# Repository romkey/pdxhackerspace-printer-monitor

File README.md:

# PDX Hackerspace 3D Printer Monitor

This is a simple device for monitoring 3D printers.

It hosts a [SeeedStudio Xiao ESP32S3 Sense](https://www.seeedstudio.com/XIAO-ESP32S3-Sense-p-5639.html) CPU camera module so that its users can see the status of their prints.

It also can use a BME280 or BME680 for environmental (air temperature and humidity) monitoring, as well as a PMS5003 for air quality/particulate matter.

It includes an optional connection to an I2C display or a larger SPI-based RGB display, and can drive an addressable RGB LED strip for lighting.

## Modifying the Xiao S3 Sense

The Xiao S3 Sense has optional D11 and D12 pins. We can use these pins
to provide PWM signals to control an optional air filter fan, and to
run optional RGB LEDs on the fan. These signals are run through the
level shifter to bring them to 5V values.

Because we've run out of pins we need to use D11 and D12. By default
they're connected to the Xiao camera board's I2S microphone. The board
needs to be modified as documented
[here](https://wiki.seeedstudio.com/xiao_esp32s3_pin_multiplexing/#step-1-cut-off-the-connection-between-j1-and-j2).
Note that this web page incorrectly states the GPIO numbers for D11
and D12. D11 is actually GPIO42 and D12 is actually GPIO41.

## PCB

The PCB is designed using KiCAD. Hardware revisions are stored in the hardware directory.

You can [order this PCB from OSHPark](https://oshpark.com/shared_projects/bLoBvODi) but please don't order it. This project is under active albeit slow development. There will be a better version available soon.

## Software

The board is intended to integrate with Home Assistant. ESPHome is the easiest way to build code for it. The repo contains an example ESPHome definition file at esphome.yml, which needs its display functionality fleshed out.

## OV5640

https://github.com/0015/ESP32-OV5640-AF

## PrusaLink

Status observed:
- finished
- idle
- busy
- attention
- printing

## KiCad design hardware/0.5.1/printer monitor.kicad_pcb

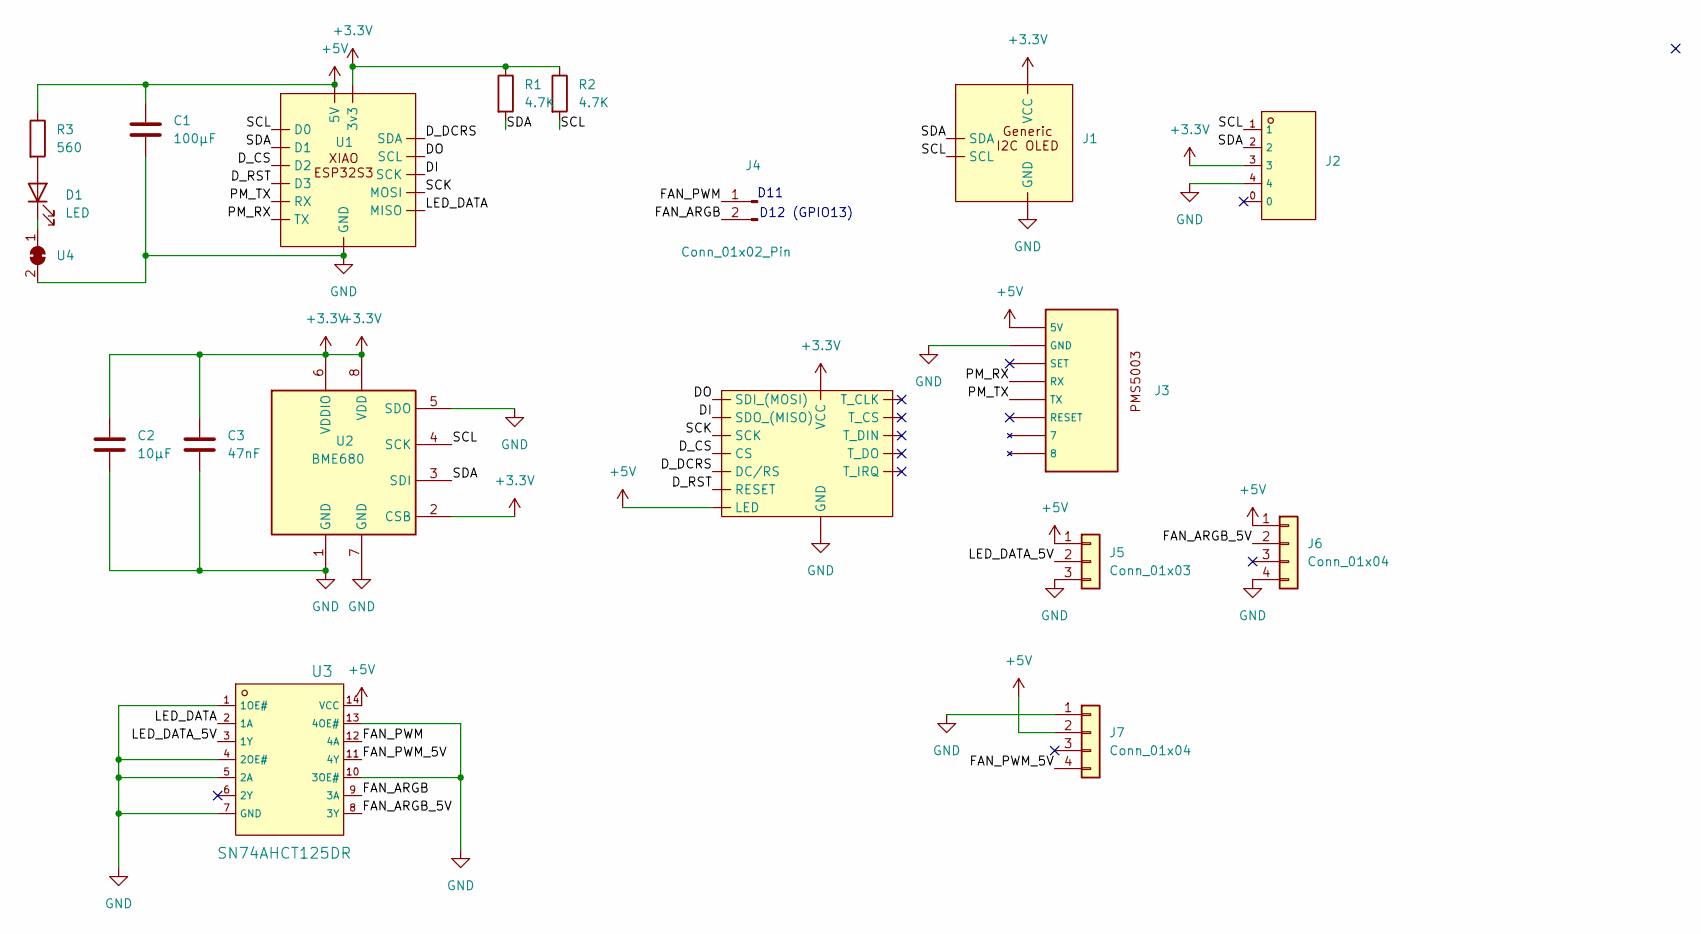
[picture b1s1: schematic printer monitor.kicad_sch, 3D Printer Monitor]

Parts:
C1: 100µF; CP_Elec_6.3x5.7; MPN C5155334
C2: 10µF; C_0805_2012Metric_Pad1.18x1.45mm_HandSolder; MPN C342724
C3: 47nF; C_0603_1608Metric_Pad1.08x0.95mm_HandSolder; MPN C123512
D1: LED; LED_1206_3216Metric_Pad1.42x1.75mm_HandSolder; MPN C375482
J1: Generic I2C OLED
J2: CONN-SMD_BM04B-SRSS-TB; MPN C160390; LCSC C160390
J3: PMS5003 Connector
J4: Conn_01x02_Pin; PinSocket_1x02_P2.54mm_Vertical
J5: Conn_01x03; PinSocket_1x03_P2.54mm_Vertical
J6, J7: Conn_01x04; PinSocket_1x04_P2.54mm_Vertical
R1, R2: 4.7K; R_0805_2012Metric_Pad1.20x1.40mm_HandSolder; MPN C105427
R3: 560; R_1206_3216Metric_Pad1.30x1.75mm_HandSolder; MPN С319525
U1: Xiao ESP32S3 Sense (Camera)
U2: BME680; Bosch_LGA-8_3x3mm_P0.8mm_ClockwisePinNumbering; MPN C125972
U3: SN74AHCT125DR; SOIC-14_L8.7-W3.9-P1.27-LS6.0-BL; MPN C155176; LCSC C155176
U4: SolderJumper-2_P1.3mm_Bridged_RoundedPad1.0x1.5mm
U5: SPI_TFT_TOUCH

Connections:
+3.3V: C2.1, C3.1, J1.4 (VCC), J2.3, R1.1, R2.1, U1.12 (3v3), U2.2 (CSB), U2.6 (VDDIO), U2.8 (VDD), U5.1 (VCC)
+5V: C1.1, J3.1 (5V), J5.1, J6.1, J7.2, R3.1, U1.14 (5V), U3.14 (VCC), U5.8 (LED)
/DI: U1.9 (SCK), U5.9 (SDO_(MISO))
/DO: U1.6 (SCL), U5.6 (SDI_(MOSI))
/D_CS: U1.3 (D2), U5.3 (CS)
/D_DCRS: U1.5 (SDA), U5.5 (DC/RS)
/D_RST: U1.4 (D3), U5.4 (RESET)
/FAN_ARGB: J4.2, U3.9 (3A)
/FAN_ARGB_5V: J6.2, U3.8 (3Y)
/FAN_PWM: J4.1, U3.12 (4A)
/FAN_PWM_5V: J7.4, U3.11 (4Y)
/LED_DATA: U1.10 (MISO), U3.2 (1A)
/LED_DATA_5V: J5.2, U3.3 (1Y)
/PM_RX: J3.4 (RX), U1.7 (TX)
/PM_TX: J3.5 (TX), U1.8 (RX)
/SCK: U1.11 (MOSI), U5.7 (SCK)
/SCL: J1.2 (SCL), J2.1, R2.2, U1.1 (D0), U2.4 (SCK)
/SDA: J1.1 (SDA), J2.2, R1.2, U1.2 (D1), U2.3 (SDI)
GND: C1.2, C2.2, C3.2, J1.3 (GND), J2.4, J3.2 (GND), J5.3, J6.4, J7.1, U1.13 (GND), U2.1 (GND), U2.5 (SDO), U2.7 (GND), U3.1 (1OE#), U3.4 (2OE#), U3.5 (2A), U3.7 (GND), U3.10 (3OE#), U3.13 (4OE#), U4.2 (B), U5.2 (GND)
unnamed: D1.2 (A), R3.2
unnamed: D1.1 (K), U4.1 (A)

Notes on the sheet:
D11
D12 (GPIO13)

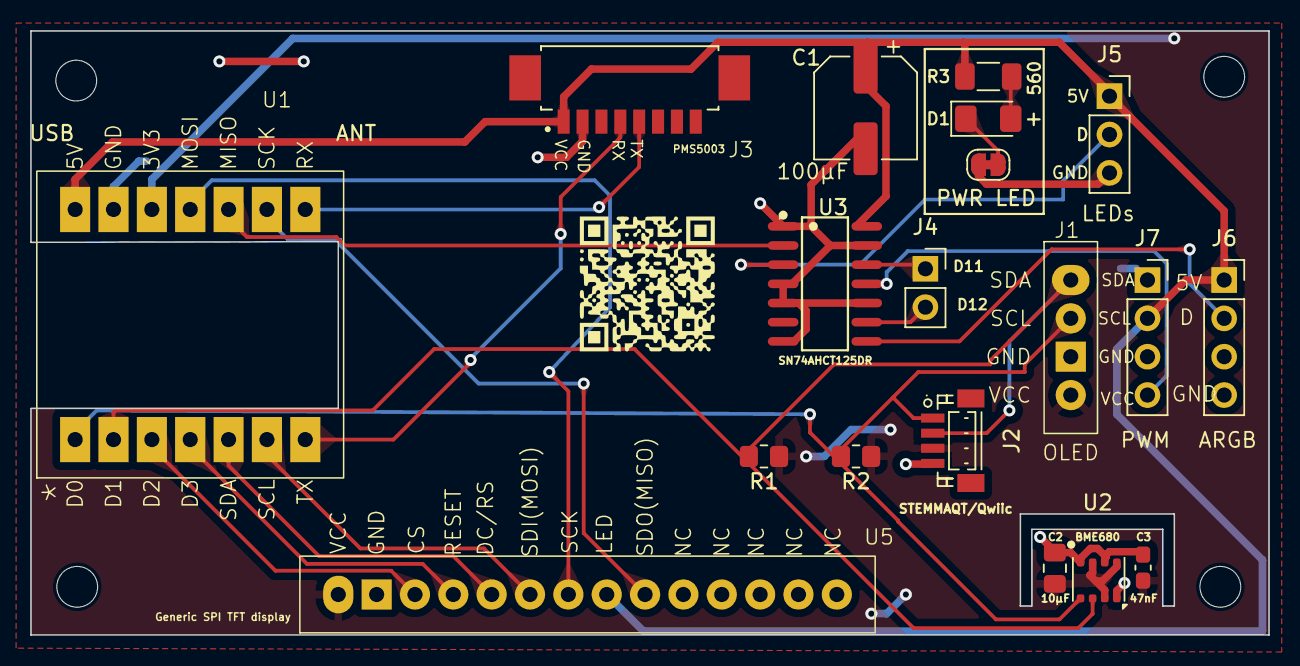
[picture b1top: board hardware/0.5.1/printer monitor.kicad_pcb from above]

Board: 2 copper layers, 82.0 x 40.0 mm, 23 parts (0 on the bottom side), 21 nets.

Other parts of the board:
H1, H2, H3, H4: MountingHole; MountingHole_2.7mm_M2.5

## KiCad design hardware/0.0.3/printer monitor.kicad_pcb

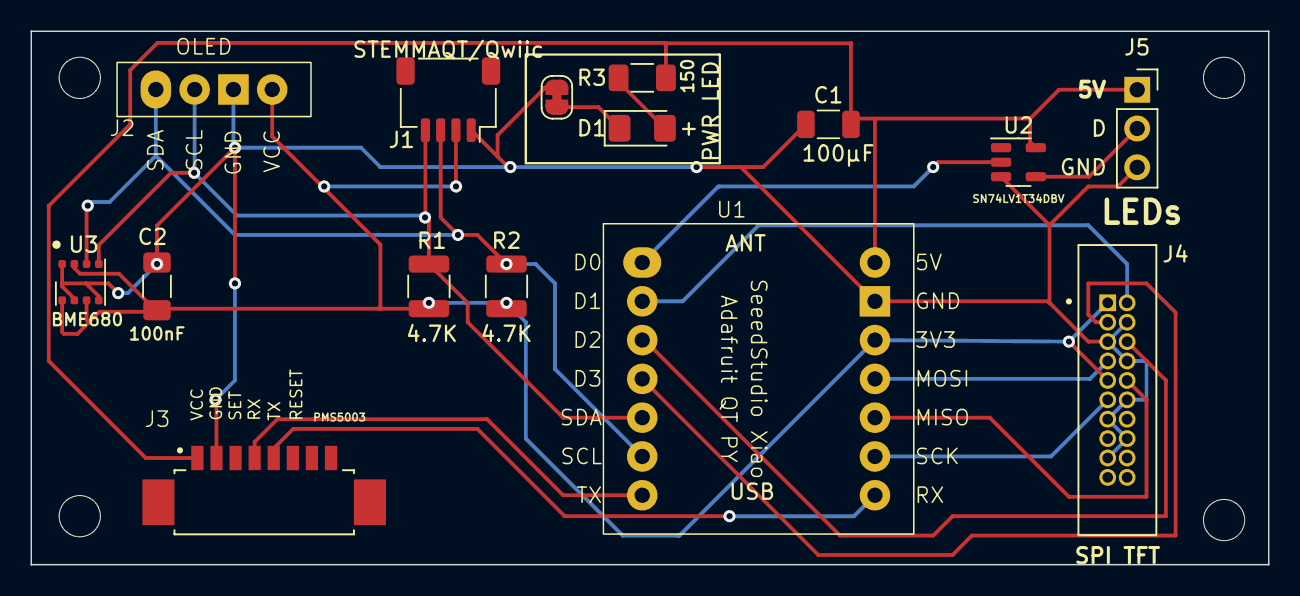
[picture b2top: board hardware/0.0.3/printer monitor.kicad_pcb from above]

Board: 2 copper layers, 81.0 x 34.9 mm, 19 parts (0 on the bottom side), 17 nets.

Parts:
C1: 100µF; C_1206_3216Metric
C2: 100nF; C_1206_3216Metric_Pad1.33x1.80mm_HandSolder
D1: LED; LED_1206_3216Metric_Pad1.42x1.75mm_HandSolder
H1, H2, H3, H4: MountingHole; MountingHole_2.7mm_M2.5
J1: JST_SH_SM04B-SRSS-TB_1x04-1MP_P1.00mm_Horizontal
J2: Generic I2C OLED
J3: PMS5003 Connector
J4: Conn_01x20; AMPHENOL_20021511-00020T4LF
J5: Conn_01x03; PinSocket_1x03_P2.54mm_Vertical
R1, R2: 4.7K; R_1210_3225Metric
R3: 150; R_1206_3216Metric_Pad1.30x1.75mm_HandSolder
U1: Xiao ESP32S3
U2: SN74LV1T34DBV; SOT-23-5
U3: BME680; Bosch_LGA-8_3x3mm_P0.8mm_ClockwisePinNumbering
U4: SolderJumper-2_P1.3mm_Bridged_RoundedPad1.0x1.5mm

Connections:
+3.3V: C2.1, J1.2 (VCC), J2.4 (VCC), J4.1, J4.9, R1.1, R2.1, U1.12 (3v3), U3.2 (CSB), U3.6 (VDDIO), U3.8 (VDD)
+5V: C1.1, J3.1 (5V), J5.1, R3.1, U1.14 (5V), U2.5 (VCC)
/DI: J4.10, U1.10 (MISO)
/DO: J4.7, U1.11 (MOSI)
/D_CS: J4.2, U1.2 (D1)
/D_DCRS: J4.6, U1.3 (D2)
/D_RST: J4.3, U1.4 (D3)
/LED_DATA: U1.1 (D0), U2.2 (A)
/PM_RX: J3.4 (RX), U1.7 (TX)
/PM_TX: J3.5 (TX), U1.8 (RX)
/SCK: J4.11, U1.9 (SCK)
/SCL: J1.4 (SCL), J2.2 (SCL), R1.2, U1.5 (SDA), U3.4 (SCK)
/SDA: J1.3 (SDA), J2.1 (SDA), R2.2, U1.6 (SCL), U3.3 (SDI)
GND: C1.2, C2.2, J1.1 (GND), J2.3 (GND), J3.2 (GND), J4.4, J4.5, J4.8, J4.12, J4.13, J4.16, J4.17, J5.3, U1.13 (GND), U2.3 (GND), U3.1 (GND), U3.5 (SDO), U3.7 (GND), U4.2 (B)
unnamed: D1.2 (A), R3.2
unnamed: D1.1 (K), U4.1 (A)
unnamed: J5.2, U2.4 (Y)

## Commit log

2024-07-01 updated esphome.yml
    new rev of board with PWM and ARGB fan support
    centered camera
    expanded SPI-TFT display header
2024-11-19 updated ESPHome definitions to work with substitutions and be includable from github
    updated KiCAD files for PCB
2024-11-19 try without display substitutions
2024-12-28 Update printer-monitor.yml
    restored some optional values, reduced SPI speed
2025-05-03 Try to fix remaining time
2025-05-03 Attempt to fix time remaining on long prints
2025-05-03 Once more into the breach
2025-08-04 Fix & improve printer display when printing
2025-08-09 camera I2C fix
    change camera definition to use defined I2C controller, i2c_pins is gone
2025-08-10 Update printer-monitor.yml
    fixed comments in C++ code
2025-08-10 Update printer-monitor.yml
    Try to fix a % problem, needs ints
2025-08-24 updated docs on Xiao S3 Sense
2025-08-24 README changes
    new printer monitor blueprint for testing
2025-08-24 fixes
2025-08-24 more blueprint fixes
2025-08-24 Update prusa_printer_monitor.yaml
    skip the default for notifications
2025-08-25 fixed some template issues in blueprint
2025-08-25 Fix some text going offscreen and handle quirks with time remaining values
2025-08-25 Remove .swp file
2025-09-05 lots of updates to printer monitor blueprint - new control for posting interval - fixed many errors - delineators around messages
2026-05-26 Add web server configuration to printer-monitor.yml
    Added web server configuration with port and version. Get rid of deprecated LED effect addressable_rainbow
2026-05-26 Remove Rainbow effect from printer monitor config
